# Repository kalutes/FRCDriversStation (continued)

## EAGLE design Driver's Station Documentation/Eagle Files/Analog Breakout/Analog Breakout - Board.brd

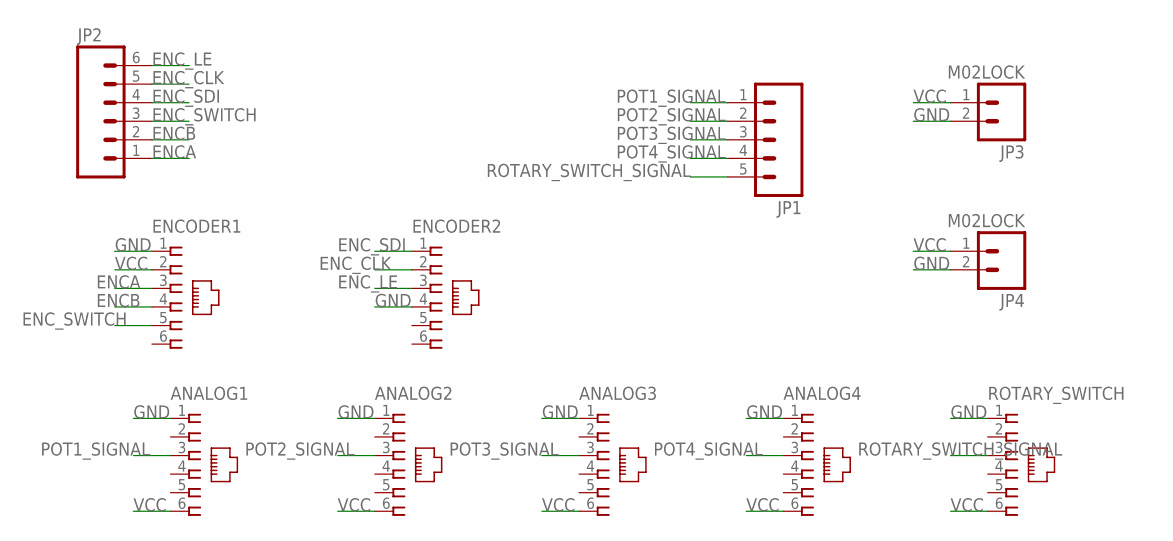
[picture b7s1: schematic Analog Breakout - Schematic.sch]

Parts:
ANALOG1, ANALOG2, ANALOG3, ANALOG4: 555165-1
ENCODER1, ENCODER2: 555165-1
JP1: M05LOCK; 1X05_LOCK
JP2: M06LOCK; 1X06_LOCK
JP3, JP4: M02LOCK; 1X02_LOCK
ROTARY_SWITCH: 555165-1

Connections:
ENCA: ENCODER1.3, JP2.1
ENCB: ENCODER1.4, JP2.2
ENC_CLK: ENCODER2.2, JP2.5
ENC_LE: ENCODER2.3, JP2.6
ENC_SDI: ENCODER2.1, JP2.4
ENC_SWITCH: ENCODER1.5, JP2.3
GND: ANALOG1.1, ANALOG2.1, ANALOG3.1, ANALOG4.1, ENCODER1.1, ENCODER2.4, JP3.2, JP4.2, ROTARY_SWITCH.1
POT1_SIGNAL: ANALOG1.3, JP1.1
POT2_SIGNAL: ANALOG2.3, JP1.2
POT3_SIGNAL: ANALOG3.3, JP1.3
POT4_SIGNAL: ANALOG4.3, JP1.4
ROTARY_SWITCH_SIGNAL: JP1.5, ROTARY_SWITCH.3
VCC: ANALOG1.6, ANALOG2.6, ANALOG3.6, ANALOG4.6, ENCODER1.2, JP3.1, JP4.1, ROTARY_SWITCH.6

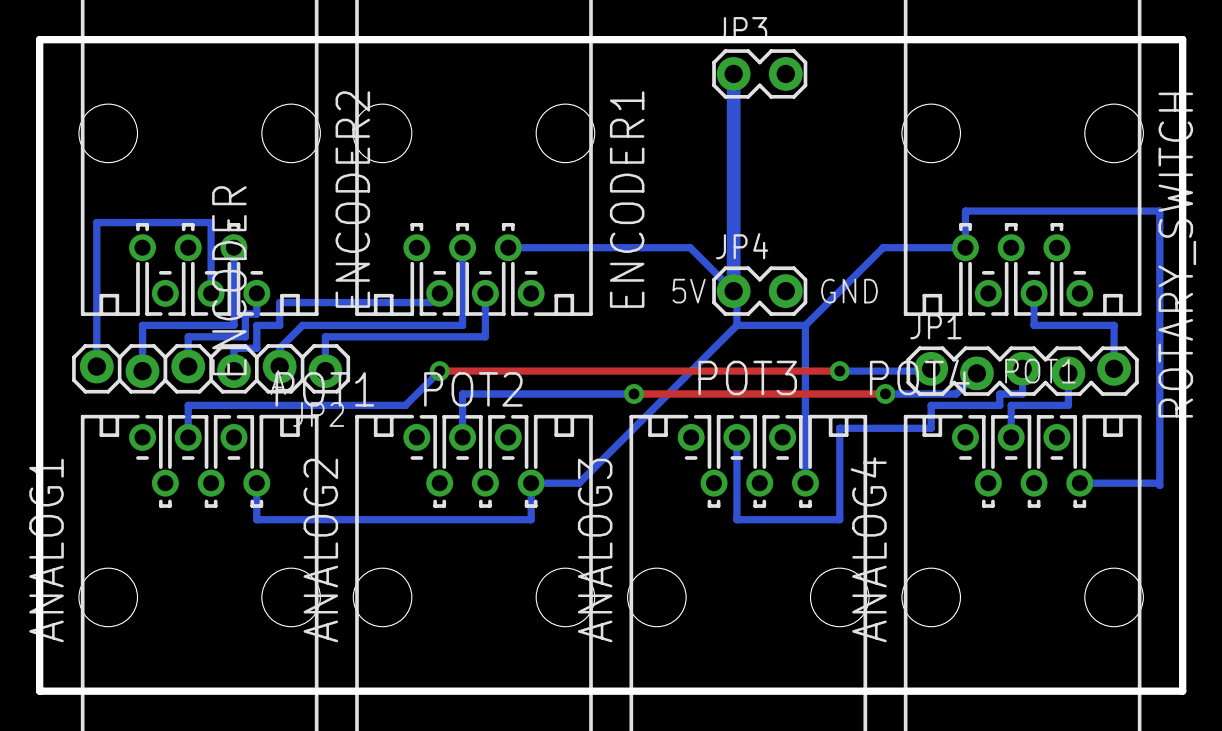
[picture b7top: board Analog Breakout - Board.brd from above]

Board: 2 copper layers, 63.5 x 36.2 mm, 11 parts (0 on the bottom side), 13 nets.
